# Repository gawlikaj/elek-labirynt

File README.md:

# elek-labirynt
Handheld Video Game

## Goals
1. Learn how to use EagleCAD (or KiCAD) to develop a PCB design for the project that will connect all hardware that the software is dependent on.
1. Write a bill of materials
1. Apply knowledge and understanding from online coursework and prior in-person coursework into an independent project. (interrupts, finite state machines, usage of GIT, interaction with an LCD display, interaction with analog devices and fundamentals of an RTOS)
1. Learn how the ESP32 microcontroller functions (and how it relates to the chosen board that I will be working with)
1. Develop drivers for SPI-controlled LCD/SD Card, I2C-controlled joystick and LiPo fuel gauge, and GPIO devices connected to the board I am using
1. Consider using and learning how a specific RTOS works such as FreeRTOS
1. Develop a hand-held game via either baremetal firmware programming or code that will run on chosen RTOS (based on #4) utilizing what I did on a text-based high school project

## Notes
The hardware documentation and any media is licensed under the Creative Commons License.  The software and its documentation are licensed under the GNU Public License.

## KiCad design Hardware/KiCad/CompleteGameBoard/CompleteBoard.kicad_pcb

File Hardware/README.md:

# elek-labirynt Hardware

Hardware Designs and bill of materials for the elek-labirynt project.  I, Andrew Gawlik, have utilized SparkFun parts, their EagleCAD library, 
and their EagleCAD files to create library parts for the schematic and PCB designs as licensed under the Creative Commons Attribution Share-Alike 4.0 License.

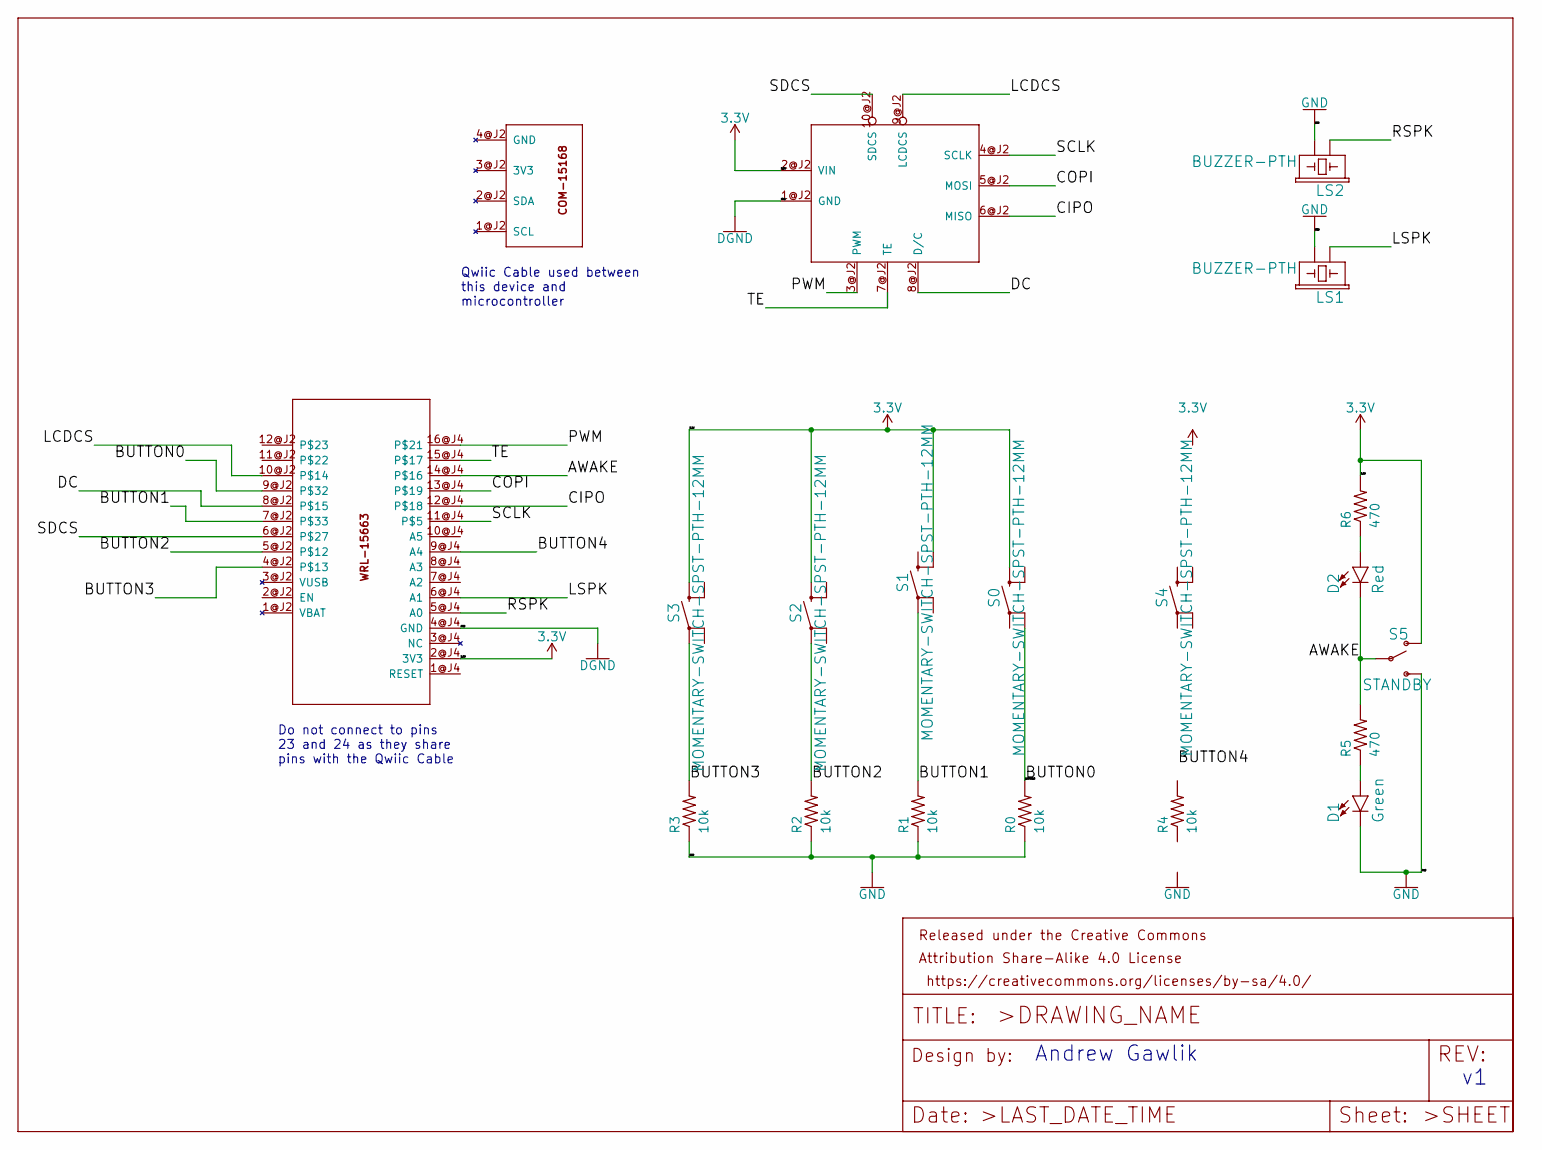
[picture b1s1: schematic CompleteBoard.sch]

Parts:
A1: ESP32_MICROCONTROLLER; WRL-17381
A2: TFT; LCD-15143
A3: COM-15168
D1: Green; LED_5MM-KIT
D2: Red; LED_5MM-KIT
FRAME1: 001; CREATIVE_COMMONS
LS1, LS2: BUZZER-PTH; BUZZER-12MM
R0, R1, R2, R3, R4: 10k; 0204_5
R5, R6: 470; 0204_5
S0, S1, S2, S3, S4: MOMENTARY-SWITCH-SPST-PTH-12MM; TACTILE_SWITCH_PTH_12MM
S5: STANDBY; SWITCH_SPDT_PTH_11.6X4.0MM

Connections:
3.3V: A1.2@J4 (3V3), A2.2@J2 (VIN), R6.2, S0.3, S1.4, S2.3, S3.3, S4.4, S5.1 (O)
AWAKE: A1.14@J4, D2.K (C), R5.2, S5.2
BUTTON0: A1.9@J2, R0.2, S0.2
BUTTON1: A1.7@J2, R1.2, S1.1
BUTTON2: A1.5@J2, R2.2, S2.1
BUTTON3: A1.4@J2, R3.2, S3.1
BUTTON4: A1.9@J4 (A4), R4.2, S4.1
CIPO: A1.12@J4, A2.6@J2 (MISO)
COPI: A1.13@J4, A2.5@J2 (MOSI)
DC: A1.8@J2, A2.8@J2 (D/C)
GND: A1.4@J4 (GND), A2.1@J2 (GND), D1.K (C), LS1.- (2), LS2.- (2), R0.1, R1.1, R2.1, R3.1, R4.1, S5.3 (S)
LCDCS: A1.10@J2, A2.9@J2 (LCDCS)
LSPK: A1.6@J4 (A1), LS1.+ (1)
unnamed: D1.A, R5.1
unnamed: D2.A, R6.1
PWM: A1.16@J4, A2.3@J2 (PWM)
RSPK: A1.5@J4 (A0), LS2.+ (1)
SCLK: A1.11@J4, A2.4@J2 (SCLK)
SDCS: A1.6@J2, A2.10@J2 (SDCS)
TE: A1.15@J4, A2.7@J2 (TE)

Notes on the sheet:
Andrew Gawlik
Qwiic Cable used between this device and microcontroller
Do not connect to pins 23 and 24 as they share pins with the Qwiic Cable

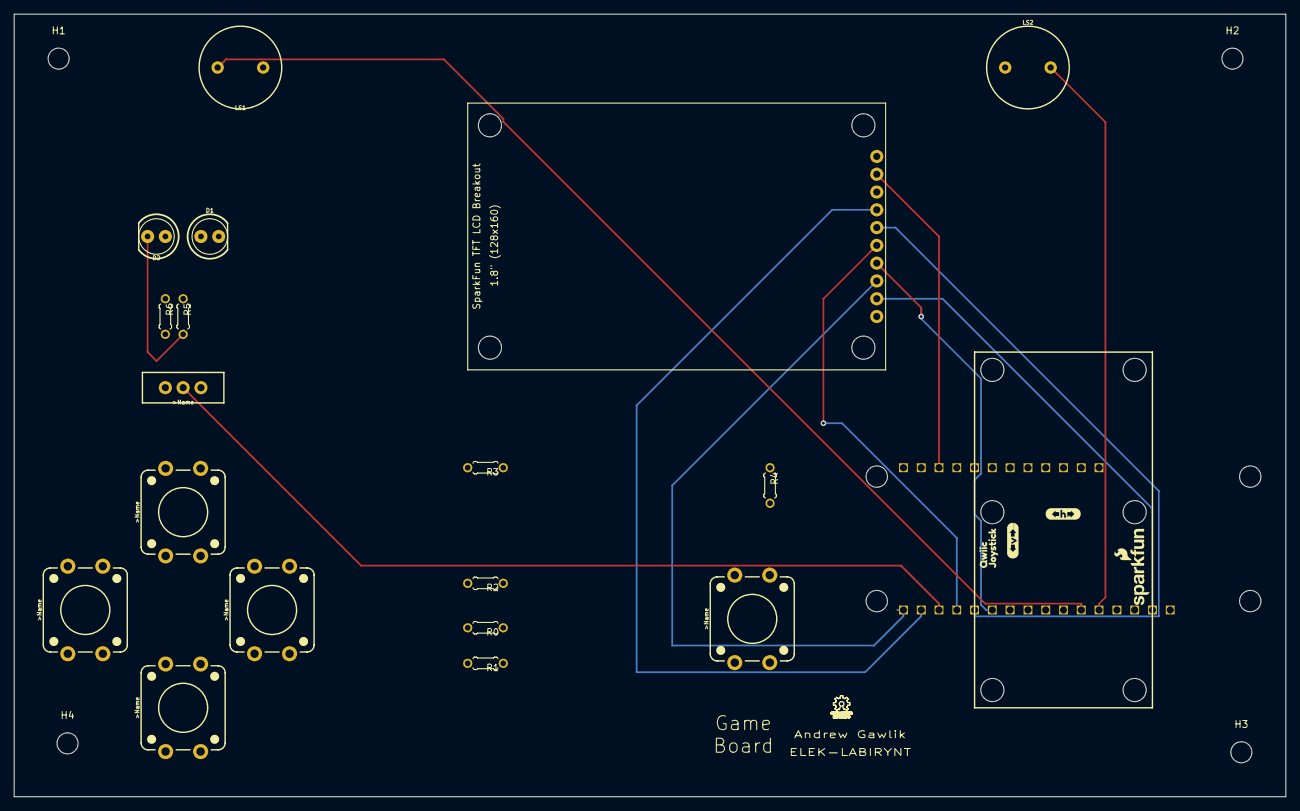
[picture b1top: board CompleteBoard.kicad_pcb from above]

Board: 4 copper layers, 181.6 x 111.8 mm, 26 parts (0 on the bottom side), 20 nets.

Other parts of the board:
FRAME1#2: 001; CREATIVE_COMMONS
H1, H2, H3, H4: MountingHole; MountingHole_3mm

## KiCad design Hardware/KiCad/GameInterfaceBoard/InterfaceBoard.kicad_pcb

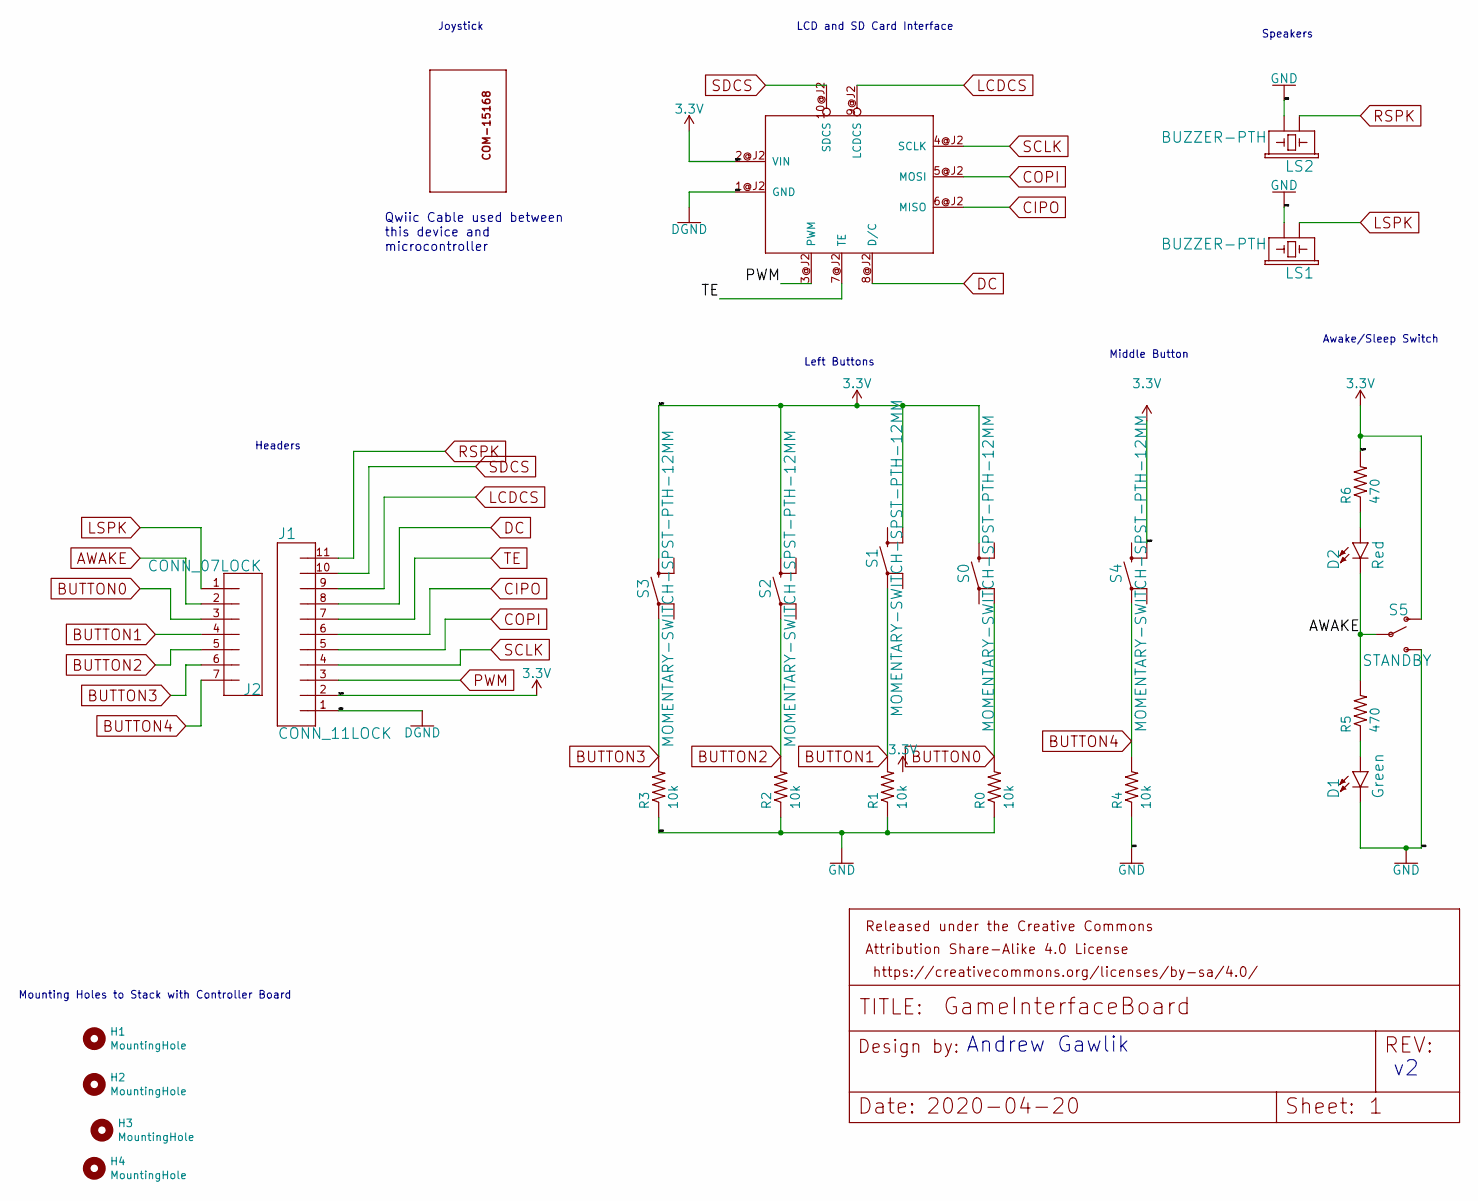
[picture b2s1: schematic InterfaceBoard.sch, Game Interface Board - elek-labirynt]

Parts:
A2: TFT; LCD-15143
A3: COM-15168
D1: Green; LED_5MM-KIT
D2: Red; LED_5MM-KIT
FRAME1: FRAME-LETTER; CREATIVE_COMMONS
H1, H2, H3, H4: MountingHole; MountingHole_3mm
J1: CONN_11LOCK; 1X11_LOCK
J2: CONN_07LOCK; 1X07_LOCK
LS1, LS2: BUZZER-PTH; BUZZER-12MM
R0, R1, R2, R3, R4: 10k; 0204_5
R5, R6: 470; 0204_5
S0, S1, S2, S3, S4: MOMENTARY-SWITCH-SPST-PTH-12MM; TACTILE_SWITCH_PTH_12MM
S5: STANDBY; SWITCH_SPDT_PTH_11.6X4.0MM

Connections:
3.3V: A2.2@J2 (VIN), J1.2, R6.2, S0.3, S1.4, S2.3, S3.3, S4.4, S5.1 (O)
/AWAKE: D2.K (C), J2.2, R5.2, S5.2
/BUTTON0: J2.3, R0.2, S0.2
/BUTTON1: J2.4, R1.2, S1.1
/BUTTON2: J2.5, R2.2, S2.1
/BUTTON3: J2.6, R3.2, S3.1
/BUTTON4: J2.7, R4.2, S4.1
/CIPO: A2.6@J2 (MISO), J1.6
/COPI: A2.5@J2 (MOSI), J1.5
/DC: A2.8@J2 (D/C), J1.8
/LCDCS: A2.9@J2 (LCDCS), J1.9
/LSPK: J2.1, LS1.+ (1)
/PWM: A2.3@J2 (PWM), J1.3
/RSPK: J1.11, LS2.+ (1)
/SCLK: A2.4@J2 (SCLK), J1.4
/SDCS: A2.10@J2 (SDCS), J1.10
/TE: A2.7@J2 (TE), J1.7
GND: A2.1@J2 (GND), D1.K (C), J1.1, LS1.- (2), LS2.- (2), R0.1, R1.1, R2.1, R3.1, R4.1, S5.3 (S)
unnamed: D1.A, R5.1
unnamed: D2.A, R6.1

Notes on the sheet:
Andrew Gawlik
Qwiic Cable used between this device and microcontroller
Headers
Left Buttons
Middle Button
Awake/Sleep Switch
Speakers
LCD and SD Card Interface
Joystick
Mounting Holes to Stack with Controller Board

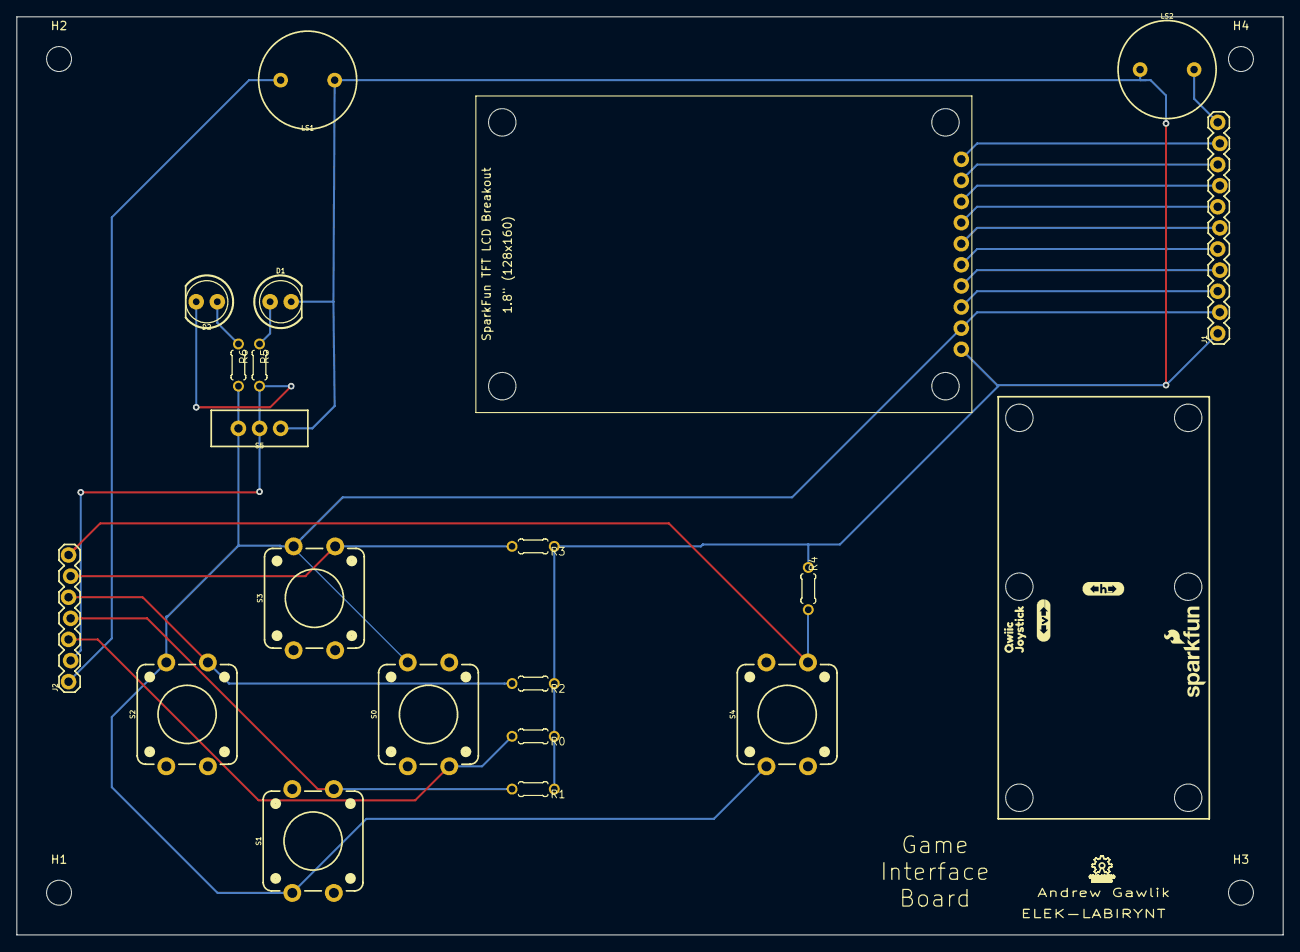
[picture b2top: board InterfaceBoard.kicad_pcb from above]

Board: 2 copper layers, 152.4 x 110.5 mm, 29 parts (0 on the bottom side), 20 nets.

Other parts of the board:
FRAME1#2, FRAME2, FRAME3: FRAME-LETTER; CREATIVE_COMMONS

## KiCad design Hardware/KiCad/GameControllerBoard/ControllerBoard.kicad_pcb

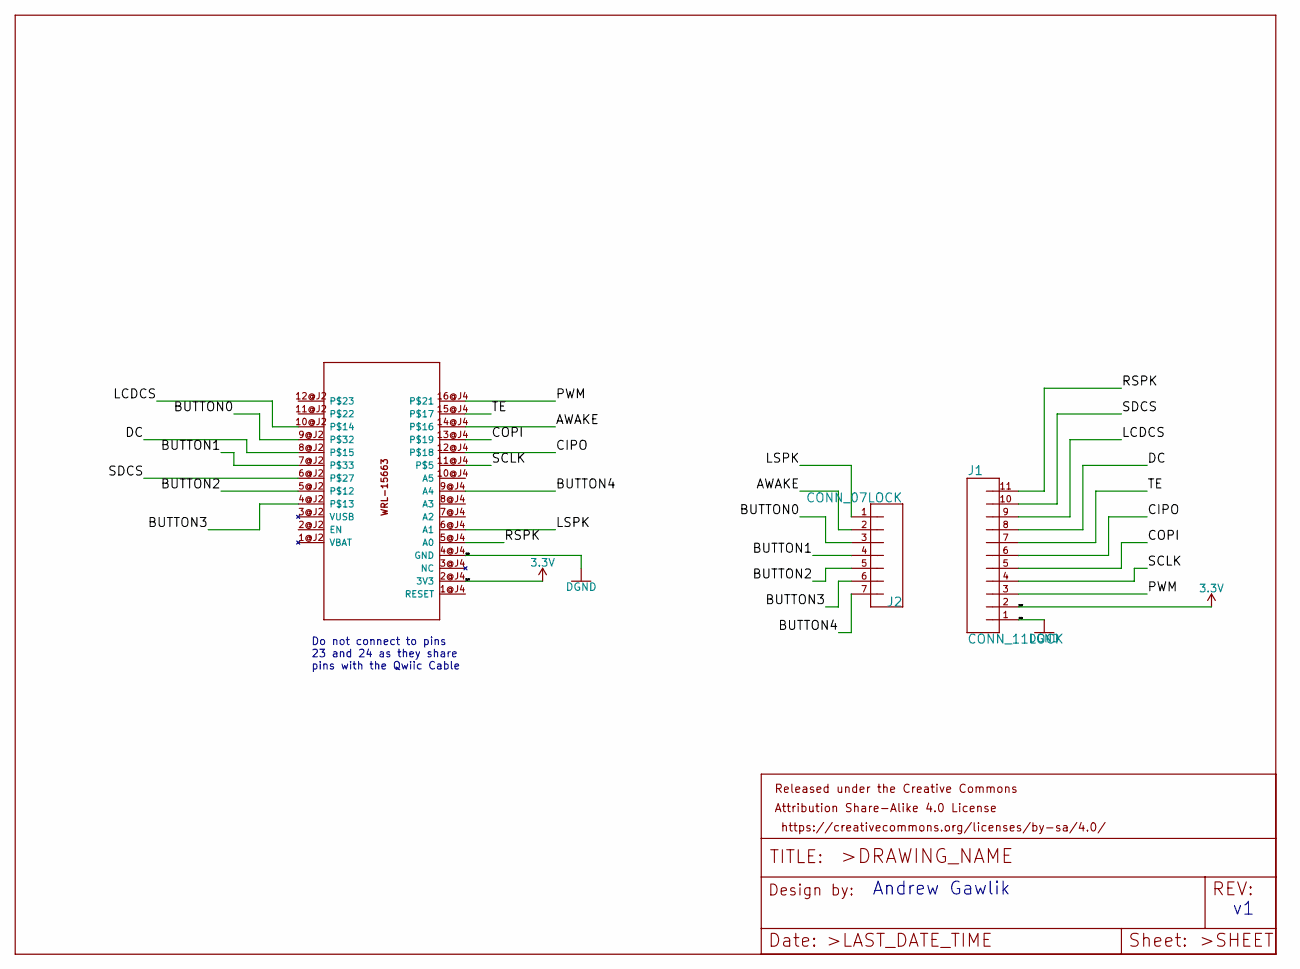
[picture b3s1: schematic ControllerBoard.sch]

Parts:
A1: ESP32_MICROCONTROLLER; WRL-17381
FRAME1: FRAME-LETTER; CREATIVE_COMMONS
J1: CONN_11LOCK; 1X11_LOCK
J2: CONN_07LOCK; 1X07_LOCK

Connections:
3.3V: A1.2@J4 (3V3), J1.2
/AWAKE: A1.14@J4, J2.2
/BUTTON0: A1.9@J2, J2.3
/BUTTON1: A1.7@J2, J2.4
/BUTTON2: A1.5@J2, J2.5
/BUTTON3: A1.4@J2, J2.6
/BUTTON4: A1.9@J4 (A4), J2.7
/CIPO: A1.12@J4, J1.6
/COPI: A1.13@J4, J1.5
/DC: A1.8@J2, J1.8
/LCDCS: A1.10@J2, J1.9
/LSPK: A1.6@J4 (A1), J2.1
/PWM: A1.16@J4, J1.3
/RSPK: A1.5@J4 (A0), J1.11
/SCLK: A1.11@J4, J1.4
/SDCS: A1.6@J2, J1.10
/TE: A1.15@J4, J1.7
GND: A1.4@J4 (GND), J1.1

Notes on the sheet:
Do not connect to pins 23 and 24 as they share pins with the Qwiic Cable
Andrew Gawlik

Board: 2 copper layers, 4 parts (0 on the bottom side), 18 nets, no tracks yet.

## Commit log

2021-02-01 Update README.md
    Added my current goals for project
2021-02-01 Update README.md
    updated numbering on goals
2021-02-01 Adding current progress of PCB design which includes GPIO buttons
2021-02-01 Adding expected bill of materials intended to be used as of 2021-02-01
2021-02-01 added 'designed by' in schematic
2021-02-01 Specified button colors and added Designed by in the PCB layout
2021-02-01 Added speakers to PCB layout
2021-02-09 Update Bill of Materials.ods
    Filled in details of draft for the Bill of Materials. At present the Custom PCB may be changed contingent on costs. A backup plan is to consider implementing on protoboards following the traces for a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
2021-02-19 Added SD card to bill of materials for the project
2021-02-19 Added LED and power switch to BOM
2021-02-19 Added the reference for the 10kOhm resistors and the extended cost; also included currency formatting.
2021-04-12 Updated BOM to reflect reduction of buttons in Issue #8
2021-04-14 First Iteration of FreeRTOS UART driver for testing microcontroller for issue #9
2021-04-14 Update README.md
    updated to reflect my own description of the driver rather than the example hello_world that was used to construct the driver
2021-04-14 Delete hello_world_main.c
    this was an example file and is not relevant to the driver I am creating...
2021-04-15 Update README.md
    included reference to KiCAD for the PCB design to allow for building the design of a PCB beyond the limitations of the free version of EagleCAD
2021-04-16 Added comments for the driver in issue #10
2021-04-16 after merge with online
2021-04-16 Update README.md
    Updated formatting for the readme and also added a notes section related to the licensing distinguishing software from other elements.
2021-04-16 Rename LICENSE to Hardware/LICENSE
    Licensing for Harware Design
2021-04-16 Create Software License
    Create the software license reflecting how the software will be licensed.
2021-04-16 Update LICENSE
    Using the same license as required from SparkFun for derived works
2021-04-17 Create README.md
    A readme describing where I have obtained my sources for the hardware contained in this project.
2021-04-17 Updated Parts on Interface board for Issue #2, need to reroute traces considering the overhaul
2021-04-17 Added Game Controller Board design for issue #7
2021-04-17 Added complete controller board minus traces for issue #12
2021-04-17 Imported Complete Game Board from EagleCAD to KiCad for work on issue #12
2021-04-19 Started placement of parts and added some traces for complete board referenced in issue #12
2021-04-20 Updated Wiring and parts for issue #12 so that through hole buttons are used
2021-04-20 Added reference for button 4 for issue #7
2021-04-20 Added connection for button 4 and updated buttons to use through hole version and switched pins for easier connection on issue #2
2021-04-20 Imported EagleCAD project into KiCad for issue #2
2021-04-20 Imported EagleCAD design to KiCad for issue #7
2021-04-20 Re-imported updated EagleCAD board for issue #12
2021-04-20 Wired Traces for PCB on issue #2
2021-04-20 Added Silk Screen, board outline and updated KiCad frame as indicated on issue #2
2021-04-20 Added OpenHardware Logo to schematic for KiCad on issue #2
2021-04-21 Added drill holes for issue #2
2021-04-21 Updated Footprints for the Interface Board as requested on issue #15
2021-04-21 Removed excess drill holes as requested on issue #17
2021-04-21 verifying changes made
2021-04-21 Completed Design Updates as identified in issue #7
2021-04-21 Controller board and interface board have been added to the drawing for separate boards version of FreeCAD assembly drawing for issue #16
2021-04-22 updated library footprints and symbols for Interface Board as indicated on #15
2021-04-22 updated library footprints and symbols for Controller Board as indicated on #15
2021-04-22 used saved library footprints and symbols from separate boards on the complete version of the board and wired all traces as per #12
2021-04-22 Created Step Export of Complete Board and Imported into FreeCad for issue #16
2021-04-22 Added Qwiic Joystick and ESP32 Thing Plus with corresponding header pins to FreeCad design for issue #16
2021-04-22 Added LCD/SD card breakout and pin headers along with the pin headers for the interface/controller board for issue #16 to the FreeCad Drawings
2021-04-23 Create Acknowledgements
    Added acknowledgements for hardware and cad drawings
2021-04-23 Added drill holes for the Joystick after reimporting the part for issue #20 the interface board is ready, however the traces need to be moved for the 'complete' board
2021-04-23 Fixed traces for the 'complete board' for issue #20
2021-04-23 Updated step export files for the boards pertaining to #20 for #16.
2021-04-29 Added reference to the m3 standoffs
    The M3 standoffs referenced in the acknowledgements include the ones chosen for the drawing and they work out really well
2021-04-29 Added reference to hex nuts used for assembly
    Added reference to the acknowledgements for the M3 hex nuts to be used in the assembly drawings
2021-04-29 Updated Complete Version of Board Assembly to include standoffs and nuts
2021-04-29 Added part hierarchy for the 'complete board'
2021-04-30 Added reference to the pinouts to help make it easier to identify which pins are available and which pins are assigned for use in driver development
2021-05-03 Reviewed the datasheets and schematics to correct the pinouts assigned to make driver development easier
2021-05-03 Updated pins for UART Driver Issue #10
2021-05-03 Added documentation for the header and source files for the UART Driver referenced in issue #10
2021-05-03 Changed name of function 'init_debug' to 'debug_init' to maintain a common naming convention and also updated comments more appropriately for issue #10
2021-05-04 Updated comments for issue #10, added new comments for the UART Driver test application
2021-05-04 added .gitignore for drivers to exclude temporary files due to opening an open document spreadsheet
2021-05-05 Updated and restructured the CMakeLists.txt and the directory layout and modularized the files for reusability for issue #10
2021-05-06 Implemented Test application using a timer with the UART debugger for issue #10
2021-05-10 Updated UART debugger driver to address issue #24 and also renamed all functions to utilize the C namespacing convention, so instead of 'debug_' it is now 'uart_debugger_' in order to make the naming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
2021-05-10 Addressed issue #25 by specifying the number of bytes to write as those received by the message buffer
2021-05-11 Added string helper for issue #26 and used for testing in the UART Debugger
2021-05-11 Made updates for issue #31 to test multiple debugger handles and failures in writing to a debugger handle. The tests were successful.
2021-05-11 Identified how to catch errors of debugger message length exceeding buffer size for issue #31
2021-05-11 Updated message to reflect timeout instead of simply error writing to message for issue #31
2021-05-11 Updated date for UART Driver and test files depicting the last date it was updated with success
2021-05-11 Removed UART Debugger from FreeRTOS version as per issue #32, locally it is moved to the Baremetal version folder which will take time to develop; the current priority lies within getting the FreeRTO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
2021-05-12 Including progress made so far on the Qwiic Joystick for issue #11, working on identifying where the problem is in regards to successful communication
2021-05-13 Update README.md
    Added updates reflecting additional peripherals being used
2021-05-14 Moved Pinouts Assigned.ods to root since it is tied to both the hardware and software
2021-05-18 added .gitignore for Hardware directory
2021-07-01 The FreeRTOS version of the button implementation is mostly implemented. There is still a problem with GPIO33 which I am trying to work out with the forums on ESP32.com
2021-07-01 Added comments to buttons component for FreeRTOS
2021-07-01 Update README.md
    Added updates to Software/README.md for inclusion of unit testing and reference to using different ports. Also updated reference to how to write the CMakeLists.txt file for custom components.
2021-07-06 Revert "Update README.md"
    This reverts commit c31bb2ba50fffefcb915850fee1989ded7c02b85.
2021-07-06 Revert "Update README.md"
    This reverts commit 1f202272569865984c632367f4be428483524e1a.
2021-07-07 Changed GPIO pin used for button1 from GPIO33 to GPIO4 and observed success
2021-07-07 Updated dates on files and the pinouts spreadsheet reflecting the changes for button1 in software for issue #36
2021-07-22 Added Calculations and Revisions to the Presentation for Momentary Pushbuttons For Issue#37

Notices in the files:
Hardware/KiCad/CompleteGameBoard/CompleteBoard.kicad_pcb:
https://creativecommons.org/licenses/by-sa/4.0
Released under the Creative Commons Attribution Share-Alike 4.0 License
